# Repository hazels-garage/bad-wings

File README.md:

# Bad Wings

* [v2](/v2) - Current Hotness
* [v1](/v1) - The Original
* [slim](/slim) - ultrathin wireless
* [pocket](/pocket) - thumb keeb
* [pocket2](/pocket2) - better thumb keeb
* [go](/go) - wireless thumb keeb
* [bold](/bold) - Oops! All 1.25u!

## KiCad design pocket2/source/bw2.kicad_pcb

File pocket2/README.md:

# Bad Wings 2: Pocket 
"Pocket" "Sized" "Ergonomic" "Keyboard"

# Features
* 36 key, "mouse" switches.
* It's really small
* HAS DIODES!
* Fits in a wallet that's slightly larger than a normal wallet.
* Could be used as a keychain, I guess.
* [Open Source](source/)
## Cases
[Top](case/top.step)
[Bottom](case/bottom.step)

## Materials
* 1x Waveshare RP2040-Zero
* 36x "Kailh Mute Button 6x6x7.3 Silent Mouse Switch"
* 36x SOD-123 Diodes

## Build Guide
* Solder diodes
* Solder switches
* Solder RP2040-zero
* Flash [firmware](FIRMWARE.md)
* Done

### Warning
I slapped together this documentation so there is a good chance I've overlooked something.  Find me on Discord if you need help.

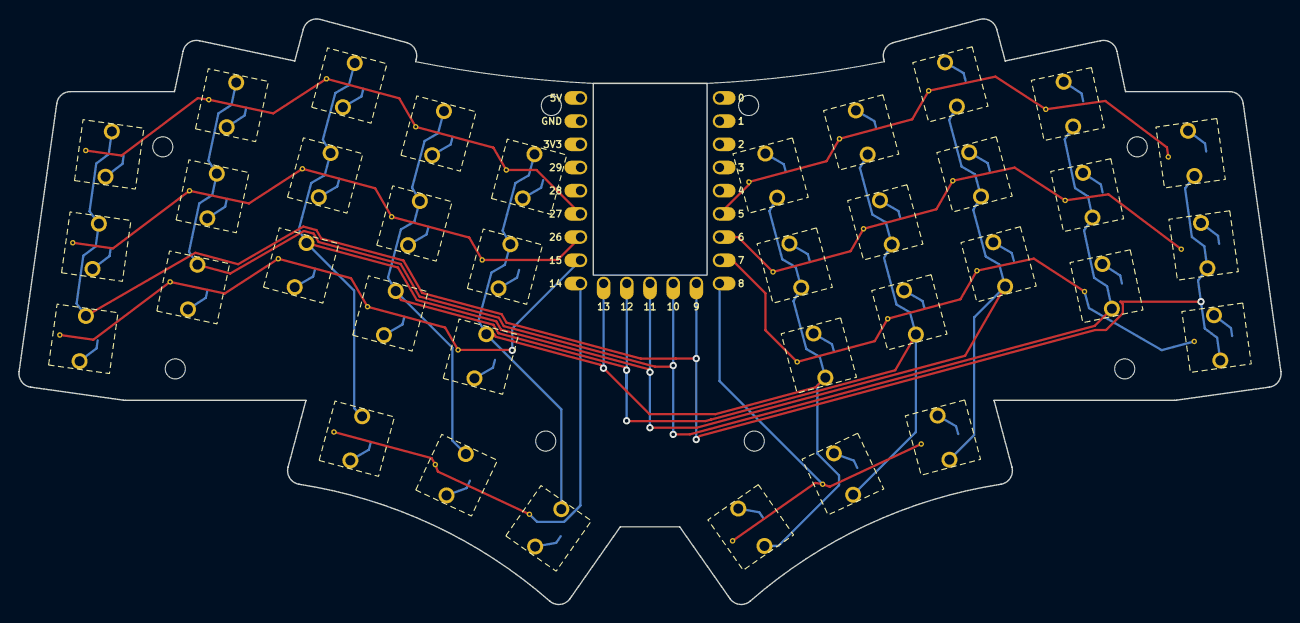
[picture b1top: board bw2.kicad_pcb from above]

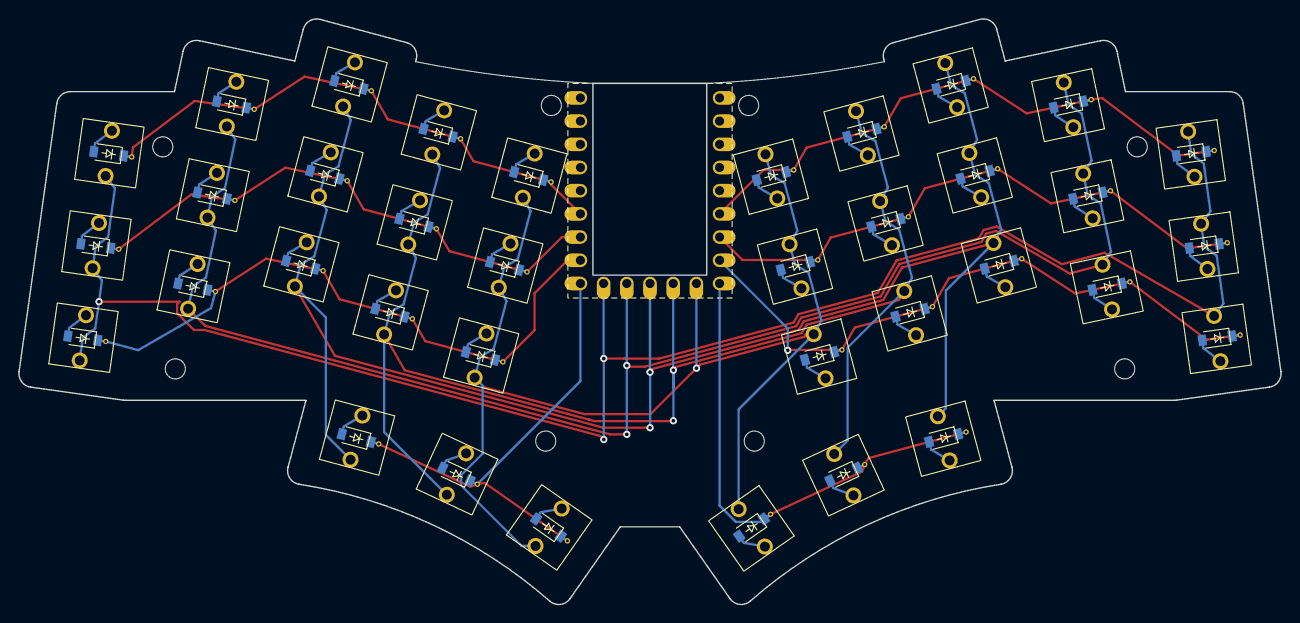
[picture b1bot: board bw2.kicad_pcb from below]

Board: 2 copper layers, 138.2 x 64.1 mm, 82 parts (44 on the bottom side), 49 nets.

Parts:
D1, D2, D3, D4, D5, D6, D7, D8, D9, D10, D11, D12, D13, D14, D15, D16, D17, D18, D19, D20, D21, D22, D23, D24, D25, D26, D27, D28, D29, D30, D31, D32, D33, D34, D35, D36: 1N4148W; D_SOD-123
H1, H2, H3, H4, H5, H6, H7, H8: MountingHole_2.2mm_M2
LOGO1: LOGO
SW1: [2,0]; Silent Square Micro Switch
SW2: [1,0]; Silent Square Micro Switch
SW3: [0,0]; Silent Square Micro Switch
SW4: [2,1]; Silent Square Micro Switch
SW5, SW8: [1,2]; Silent Square Micro Switch
SW6: [0,1]; Silent Square Micro Switch
SW7: [2,2]; Silent Square Micro Switch
SW9: [0,2]; Silent Square Micro Switch
SW10: [2,3]; Silent Square Micro Switch
SW11: [1,3]; Silent Square Micro Switch
SW12: [0,3]; Silent Square Micro Switch
SW13: [2,4]; Silent Square Micro Switch
SW14: [1,4]; Silent Square Micro Switch
SW15: [0,4]; Silent Square Micro Switch
SW16: [6,0]; Silent Square Micro Switch
SW17: [5,0]; Silent Square Micro Switch
SW18: [4,0]; Silent Square Micro Switch
SW19: [6,1]; Silent Square Micro Switch
SW20: [5,1]; Silent Square Micro Switch
SW21: [4,1]; Silent Square Micro Switch
SW22: [6,2]; Silent Square Micro Switch
SW23: [5,2]; Silent Square Micro Switch
SW24: [4,2]; Silent Square Micro Switch
SW25: [6,3]; Silent Square Micro Switch
SW26: [5,3]; Silent Square Micro Switch
SW27: [4,3]; Silent Square Micro Switch
SW28: [6,4]; Silent Square Micro Switch
SW29: [5,4]; Silent Square Micro Switch
SW30: [4,4]; Silent Square Micro Switch
SW31: [3,2]; Silent Square Micro Switch
SW32: [3,3]; Silent Square Micro Switch
SW33: [3,4]; Silent Square Micro Switch
SW34: [7,2]; Silent Square Micro Switch
SW35: [7,3]; Silent Square Micro Switch
SW36: [7,4]; Silent Square Micro Switch
U1: RP2040-Zero; rp2040-zero-facedown-swapped-5v-gnd

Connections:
COL0: SW1.2, SW2.2, SW3.2, SW16.2, SW17.2, SW18.2, U1.10 (GP9)
COL1: SW4.2, SW5.2, SW6.2, SW19.2, SW20.2, SW21.2, U1.11 (GP10)
COL2: SW7.2, SW8.2, SW9.2, SW22.2, SW23.2, SW24.2, SW31.2, SW34.2, U1.12 (GP11)
COL3: SW10.2, SW11.2, SW12.2, SW25.2, SW26.2, SW27.2, SW32.2, SW35.2, U1.13 (GP12)
COL4: SW13.2, SW14.2, SW15.2, SW28.2, SW29.2, SW30.2, SW33.2, SW36.2, U1.14 (GP13)
unnamed: D1.2 (A), SW1.1
unnamed: D2.2 (A), SW2.1
unnamed: D3.2 (A), SW3.1
unnamed: D4.2 (A), SW4.1
unnamed: D5.2 (A), SW5.1
unnamed: D6.2 (A), SW6.1
unnamed: D7.2 (A), SW7.1
unnamed: D8.2 (A), SW8.1
unnamed: D9.2 (A), SW9.1
unnamed: D10.2 (A), SW10.1
unnamed: D11.2 (A), SW11.1
unnamed: D12.2 (A), SW12.1
unnamed: D13.2 (A), SW13.1
unnamed: D14.2 (A), SW14.1
unnamed: D15.2 (A), SW15.1
unnamed: D16.2 (A), SW16.1
unnamed: D17.2 (A), SW17.1
unnamed: D18.2 (A), SW18.1
unnamed: D19.2 (A), SW19.1
unnamed: D20.2 (A), SW20.1
unnamed: D21.2 (A), SW21.1
unnamed: D22.2 (A), SW22.1
unnamed: D23.2 (A), SW23.1
unnamed: D24.2 (A), SW24.1
unnamed: D25.2 (A), SW25.1
unnamed: D26.2 (A), SW26.1
unnamed: D27.2 (A), SW27.1
unnamed: D28.2 (A), SW28.1
unnamed: D29.2 (A), SW29.1
unnamed: D30.2 (A), SW30.1
unnamed: D31.2 (A), SW31.1
unnamed: D32.2 (A), SW32.1
unnamed: D33.2 (A), SW33.1
unnamed: D34.2 (A), SW34.1
unnamed: D35.2 (A), SW35.1
unnamed: D36.2 (A), SW36.1
ROW0: D3.1 (K), D6.1 (K), D9.1 (K), D12.1 (K), D15.1 (K), U1.18 (GP27)
ROW1: D2.1 (K), D5.1 (K), D8.1 (K), D11.1 (K), D14.1 (K), U1.17 (GP26)
ROW2: D1.1 (K), D4.1 (K), D7.1 (K), D10.1 (K), D13.1 (K), U1.16 (GP15)
ROW3: D31.1 (K), D32.1 (K), D33.1 (K), U1.15 (GP14)
ROW4: D18.1 (K), D21.1 (K), D24.1 (K), D27.1 (K), D30.1 (K), U1.6 (GP5)
ROW5: D17.1 (K), D20.1 (K), D23.1 (K), D26.1 (K), D29.1 (K), U1.7 (GP6)
ROW6: D16.1 (K), D19.1 (K), D22.1 (K), D25.1 (K), D28.1 (K), U1.8 (GP7)
ROW7: D34.1 (K), D35.1 (K), D36.1 (K), U1.9 (GP8)

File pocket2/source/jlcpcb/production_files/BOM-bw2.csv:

Comment,Designator,Footprint,LCSC,Quantity
,H1,MountingHole_2.2mm_M2,,1
,H2,MountingHole_2.2mm_M2,,1
RP2040-Zero,U1,rp2040-zero-facedown-swapped-5v-gnd,,1
,H3,MountingHole_2.2mm_M2,,1
,H4,MountingHole_2.2mm_M2,,1
,H5,MountingHole_2.2mm_M2,,1
,H6,MountingHole_2.2mm_M2,,1
,H7,MountingHole_2.2mm_M2,,1
,H8,MountingHole_2.2mm_M2,,1
"[7,4]",SW36,Silent Square Micro Switch,,1
"[7,3]",SW35,Silent Square Micro Switch,,1
"[7,2]",SW34,Silent Square Micro Switch,,1
"[3,4]",SW33,Silent Square Micro Switch,,1
"[3,3]",SW32,Silent Square Micro Switch,,1
"[3,2]",SW31,Silent Square Micro Switch,,1
"[4,4]",SW30,Silent Square Micro Switch,,1
"[5,4]",SW29,Silent Square Micro Switch,,1
"[6,4]",SW28,Silent Square Micro Switch,,1
"[4,3]",SW27,Silent Square Micro Switch,,1
"[5,3]",SW26,Silent Square Micro Switch,,1
"[6,3]",SW25,Silent Square Micro Switch,,1
"[4,2]",SW24,Silent Square Micro Switch,,1
"[5,2]",SW23,Silent Square Micro Switch,,1
"[6,2]",SW22,Silent Square Micro Switch,,1
"[4,1]",SW21,Silent Square Micro Switch,,1
"[5,1]",SW20,Silent Square Micro Switch,,1
"[6,1]",SW19,Silent Square Micro Switch,,1
"[4,0]",SW18,Silent Square Micro Switch,,1
"[5,0]",SW17,Silent Square Micro Switch,,1
"[6,0]",SW16,Silent Square Micro Switch,,1
"[0,4]",SW15,Silent Square Micro Switch,,1
"[1,4]",SW14,Silent Square Micro Switch,,1
"[2,4]",SW13,Silent Square Micro Switch,,1
"[0,3]",SW12,Silent Square Micro Switch,,1
"[1,3]",SW11,Silent Square Micro Switch,,1
"[2,3]",SW10,Silent Square Micro Switch,,1
"[0,2]",SW9,Silent Square Micro Switch,,1
"[1,2]",SW8,Silent Square Micro Switch,,1
"[2,2]",SW7,Silent Square Micro Switch,,1
"[0,1]",SW6,Silent Square Micro Switch,,1
"[1,2]",SW5,Silent Square Micro Switch,,1
"[2,1]",SW4,Silent Square Micro Switch,,1
"[0,0]",SW3,Silent Square Micro Switch,,1
"[1,0]",SW2,Silent Square Micro Switch,,1
"[2,0]",SW1,Silent Square Micro Switch,,1
1N4148W,D36,D_SOD-123,,1
1N4148W,D35,D_SOD-123,,1
1N4148W,D34,D_SOD-123,,1
1N4148W,D33,D_SOD-123,,1
1N4148W,D32,D_SOD-123,,1
1N4148W,D31,D_SOD-123,,1
1N4148W,D30,D_SOD-123,,1
1N4148W,D29,D_SOD-123,,1
1N4148W,D28,D_SOD-123,,1
1N4148W,D27,D_SOD-123,,1
1N4148W,D26,D_SOD-123,,1
1N4148W,D25,D_SOD-123,,1
1N4148W,D24,D_SOD-123,,1
1N4148W,D23,D_SOD-123,,1
1N4148W,D22,D_SOD-123,,1
1N4148W,D21,D_SOD-123,,1
1N4148W,D20,D_SOD-123,,1
1N4148W,D19,D_SOD-123,,1
1N4148W,D18,D_SOD-123,,1
1N4148W,D17,D_SOD-123,,1
1N4148W,D16,D_SOD-123,,1
1N4148W,D15,D_SOD-123,,1
1N4148W,D14,D_SOD-123,,1
1N4148W,D13,D_SOD-123,,1
1N4148W,D12,D_SOD-123,,1
1N4148W,D11,D_SOD-123,,1
1N4148W,D10,D_SOD-123,,1
1N4148W,D9,D_SOD-123,,1
1N4148W,D8,D_SOD-123,,1
1N4148W,D7,D_SOD-123,,1
1N4148W,D6,D_SOD-123,,1
1N4148W,D5,D_SOD-123,,1
1N4148W,D4,D_SOD-123,,1
1N4148W,D3,D_SOD-123,,1
1N4148W,D2,D_SOD-123,,1
1N4148W,D1,D_SOD-123,,1
,LOGO1,LOGO,,1

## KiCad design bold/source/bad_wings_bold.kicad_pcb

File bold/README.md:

# Bad Wings: **Bold**
Oops! All 1.25u!

# Features
* 36key, "choc spaced", all 1.25u
* RP2040-Zero

# Materials
* 1x RP2040-zero
* 36x Choc v1 Switches
* 36x SOD-123 1N4148 Diodes
* 36x Hotswap Sockets (optional)

# Build Guide
* Install Diodes
* Install RP2040-zero (buttons facing up)
* Flash [Firmware](FIRMWARE.md)
* Test Matrix
  * use metal tweezers to short the connections for each switch on the PCB
* If matrix works, install switches
  * Hotswap Sockets optional
  * ALso mill-maxable
* Done

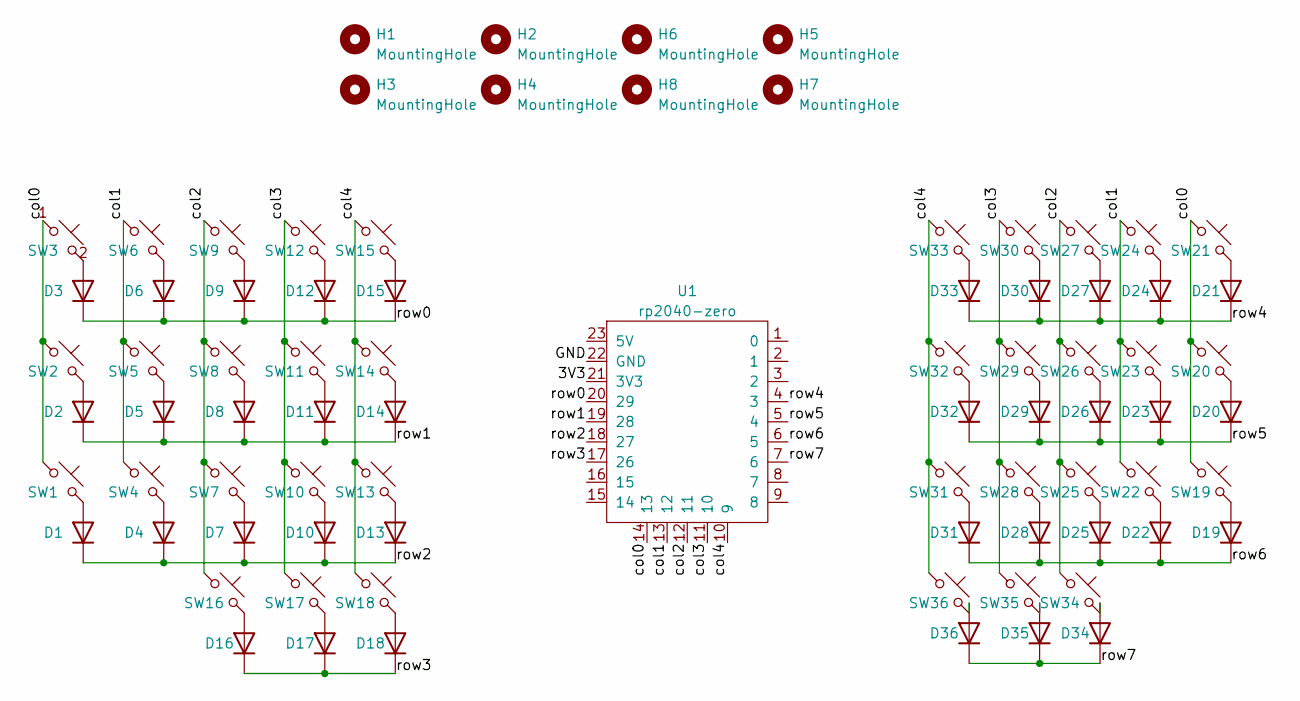
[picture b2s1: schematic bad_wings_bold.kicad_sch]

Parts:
D1, D2, D3, D4, D5, D6, D7, D8, D9, D10, D11, D12, D13, D14, D15, D16, D17, D18, D19, D20, D21, D22, D23, D24, D25, D26, D27, D28, D29, D30, D31, D32, D33, D34, D35, D36: 1N4148W; D_SOD-123
H1, H2, H3, H4, H5, H6, H7, H8: MountingHole; MountingHole_3.2mm_M3
SW1, SW2, SW3, SW4, SW5, SW6, SW7, SW8, SW9, SW10, SW11, SW12, SW13, SW14, SW15, SW16, SW17, SW18, SW19, SW20, SW21, SW22, SW23, SW24, SW25, SW26, SW27, SW28, SW29, SW30, SW31, SW32, SW33, SW34, SW35, SW36: SW_Push_45deg; Choc-1u-hotswap-solderable
U1: rp2040-zero; rp2040-zero-facedown

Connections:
/3V3: U1.21 (3V3)
/GND: U1.22 (GND)
/col0: SW1.1, SW2.1, SW3.1, SW19.1, SW20.1, SW21.1, U1.14 (13)
/col1: SW4.1, SW5.1, SW6.1, SW22.1, SW23.1, SW24.1, U1.13 (12)
/col2: SW7.1, SW8.1, SW9.1, SW16.1, SW25.1, SW26.1, SW27.1, SW34.1, U1.12 (11)
/col3: SW10.1, SW11.1, SW12.1, SW17.1, SW28.1, SW29.1, SW30.1, SW35.1, U1.11 (10)
/col4: SW13.1, SW14.1, SW15.1, SW18.1, SW31.1, SW32.1, SW33.1, SW36.1, U1.10 (9)
/row0: D3.1 (K), D6.1 (K), D9.1 (K), D12.1 (K), D15.1 (K), U1.20 (29)
/row1: D2.1 (K), D5.1 (K), D8.1 (K), D11.1 (K), D14.1 (K), U1.19 (28)
/row2: D1.1 (K), D4.1 (K), D7.1 (K), D10.1 (K), D13.1 (K), U1.18 (27)
/row3: D16.1 (K), D17.1 (K), D18.1 (K), U1.17 (26)
/row4: D21.1 (K), D24.1 (K), D27.1 (K), D30.1 (K), D33.1 (K), U1.4 (3)
/row5: D20.1 (K), D23.1 (K), D26.1 (K), D29.1 (K), D32.1 (K), U1.5 (4)
/row6: D19.1 (K), D22.1 (K), D25.1 (K), D28.1 (K), D31.1 (K), U1.6 (5)
/row7: D34.1 (K), D35.1 (K), D36.1 (K), U1.7 (6)
unnamed: D1.2 (A), SW1.2
unnamed: D2.2 (A), SW2.2
unnamed: D3.2 (A), SW3.2
unnamed: D4.2 (A), SW4.2
unnamed: D5.2 (A), SW5.2
unnamed: D6.2 (A), SW6.2
unnamed: D7.2 (A), SW7.2
unnamed: D8.2 (A), SW8.2
unnamed: D9.2 (A), SW9.2
unnamed: D10.2 (A), SW10.2
unnamed: D11.2 (A), SW11.2
unnamed: D12.2 (A), SW12.2
unnamed: D13.2 (A), SW13.2
unnamed: D14.2 (A), SW14.2
unnamed: D15.2 (A), SW15.2
unnamed: D16.2 (A), SW16.2
unnamed: D17.2 (A), SW17.2
unnamed: D18.2 (A), SW18.2
unnamed: D19.2 (A), SW19.2
unnamed: D20.2 (A), SW20.2
unnamed: D21.2 (A), SW21.2
unnamed: D22.2 (A), SW22.2
unnamed: D23.2 (A), SW23.2
unnamed: D24.2 (A), SW24.2
unnamed: D25.2 (A), SW25.2
unnamed: D26.2 (A), SW26.2
unnamed: D27.2 (A), SW27.2
unnamed: D28.2 (A), SW28.2
unnamed: D29.2 (A), SW29.2
unnamed: D30.2 (A), SW30.2
unnamed: D31.2 (A), SW31.2
unnamed: D32.2 (A), SW32.2
unnamed: D33.2 (A), SW33.2
unnamed: D34.2 (A), SW34.2
unnamed: D35.2 (A), SW35.2
unnamed: D36.2 (A), SW36.2

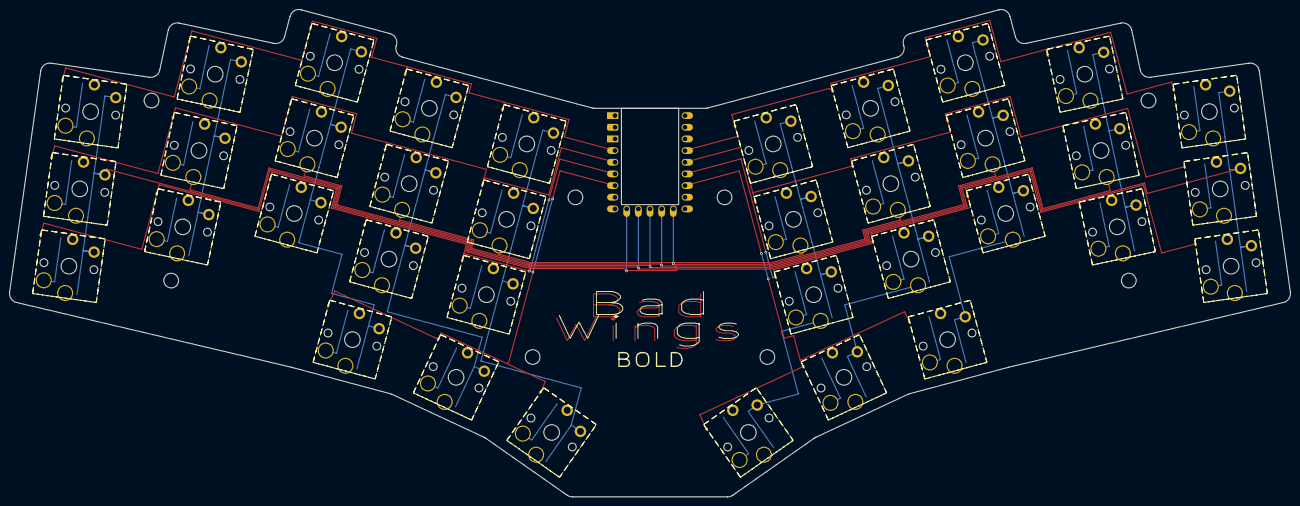
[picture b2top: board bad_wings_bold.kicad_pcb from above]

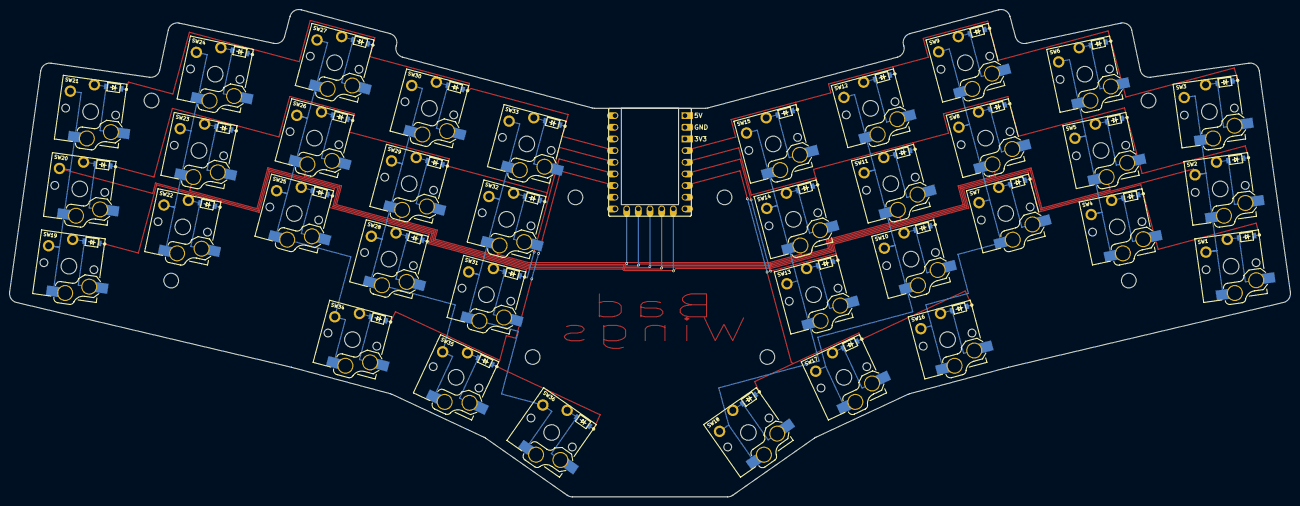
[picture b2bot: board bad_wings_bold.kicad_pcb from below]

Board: 2 copper layers, 279.0 x 106.2 mm, 81 parts (36 on the bottom side), 49 nets.

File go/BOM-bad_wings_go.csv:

Comment,Designator,Footprint,LCSC
SW_Push_45deg,"SW1,SW10,SW11,SW12,SW13,SW14,SW15,SW16,SW17,SW18,SW19,SW2,SW20,SW21,SW22,SW23,SW24,SW25,SW26,SW27,SW28,SW29,SW3,SW30,SW31,SW32,SW33,SW34,SW35,SW36,SW4,SW5,SW6,SW7,SW8,SW9",SW_SPST_TL3342,C115351
SW_SPDT,PWR1,SPDT_C128955,C128955
1N4148W,BD1,D_SOD-123,C81598
xiao-ble,U1,xiao-ble-smd-cutout,

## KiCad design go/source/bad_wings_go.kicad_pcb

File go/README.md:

# Bad Wings: Go
Wireless "Pocket" "Sized" "Ergonomic" "Keyboard"

# Features
* 36 key, 4x4mm switches.
* It's really small
* No diodes, so don't try to type fast
* Fits in a wallet that's slightly larger than a normal wallet.
* Could be used as a keychain, I guess.
* [Open Source](source/)

## Materials
* 1x XIAO BLE
* 1x SOD-123 1N4148 Diode
* 36x SKQGAFE010 TACT Switch
* 1x MSK-12C02 Power Switch
* 1x [CR2032 Battery Holder](https://www.aliexpress.us/item/2251832843180857.html)
## Build Guide
* Solder switches
* Solder XIAO
  * Surface mounted on top of PCB
  * Solder BAT and NFC pads from back of PCB
* Flash [firmware](FIRMWARE.md)
* Solder CR2032 holder
* Solder battery diode
* Solder Power Switch
* Insert Battery
* Done

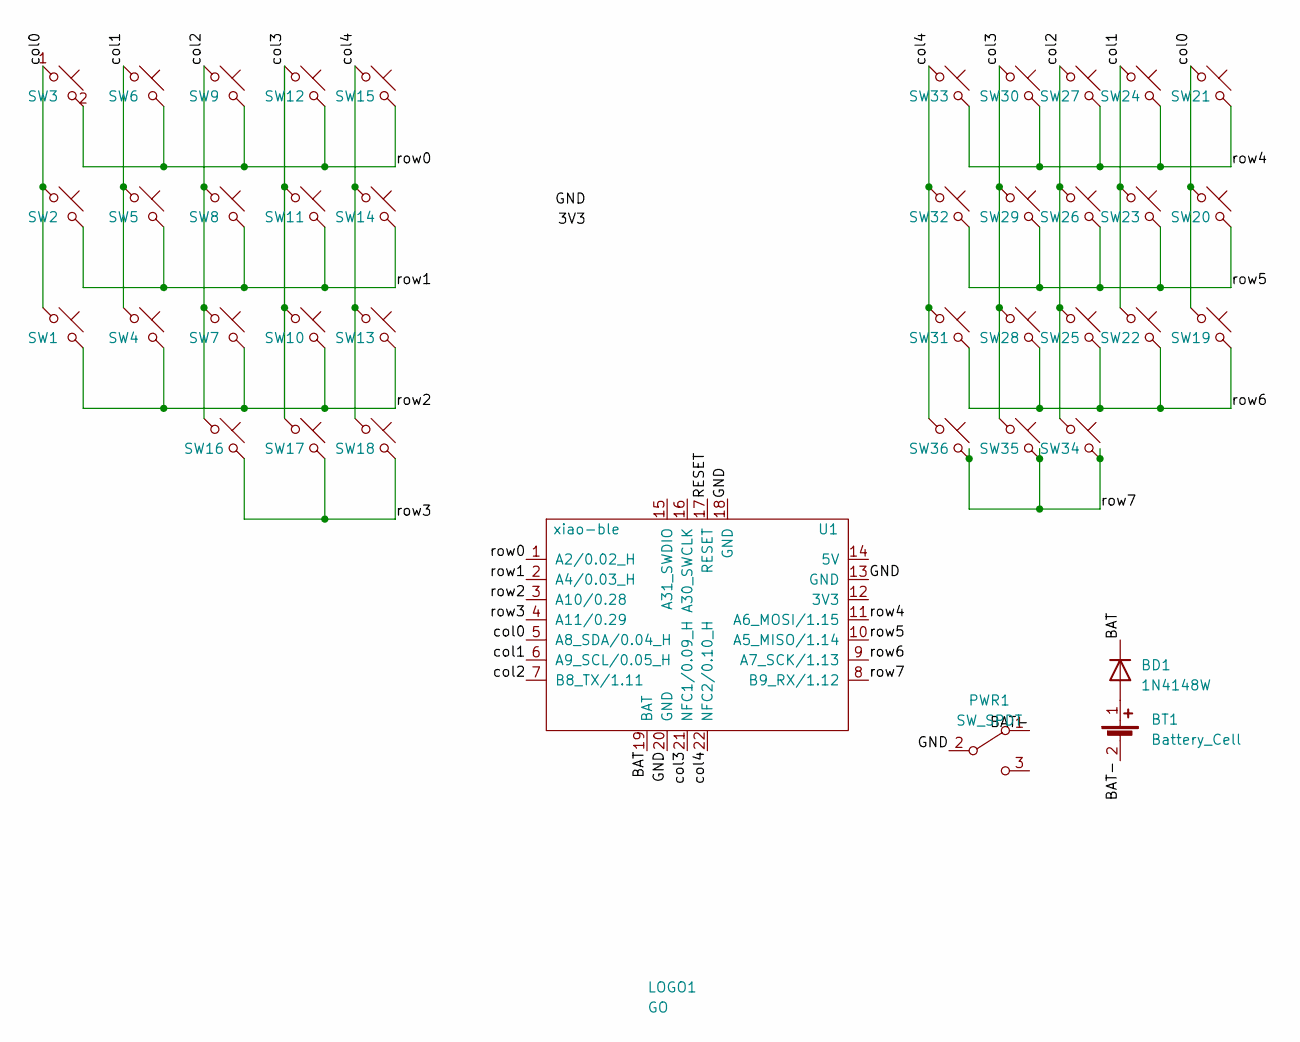
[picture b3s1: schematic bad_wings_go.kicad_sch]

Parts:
BD1: 1N4148W; D_SOD-123
BT1: Battery_Cell; BatteryHolder_Keystone_3002_1x2032
LOGO1: GO; logo
PWR1: SW_SPDT; SPDT_C128955
SW1, SW2, SW3, SW4, SW5, SW6, SW7, SW8, SW9, SW10, SW11, SW12, SW13, SW14, SW15, SW16, SW17, SW18, SW19, SW20, SW21, SW22, SW23, SW24, SW25, SW26, SW27, SW28, SW29, SW30, SW31, SW32, SW33, SW34, SW35, SW36: SW_Push_45deg; SW_SPST_TL3342
U1: xiao-ble; xiao-ble-smd-cutout

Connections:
/BAT: BD1.1 (K), U1.19 (BAT)
/BAT-: BT1.2 (-), PWR1.1 (A)
/GND: PWR1.2 (B), U1.13 (GND), U1.18 (GND), U1.20 (GND)
/RESET: U1.17 (RESET)
/col0: SW1.1, SW2.1, SW3.1, SW19.1, SW20.1, SW21.1, U1.5 (A8_SDA/0.04_H)
/col1: SW4.1, SW5.1, SW6.1, SW22.1, SW23.1, SW24.1, U1.6 (A9_SCL/0.05_H)
/col2: SW7.1, SW8.1, SW9.1, SW16.1, SW25.1, SW26.1, SW27.1, SW34.1, U1.7 (B8_TX/1.11)
/col3: SW10.1, SW11.1, SW12.1, SW17.1, SW28.1, SW29.1, SW30.1, SW35.1, U1.21 (NFC1/0.09_H)
/col4: SW13.1, SW14.1, SW15.1, SW18.1, SW31.1, SW32.1, SW33.1, SW36.1, U1.22 (NFC2/0.10_H)
/row0: SW3.2, SW6.2, SW9.2, SW12.2, SW15.2, U1.1 (A2/0.02_H)
/row1: SW2.2, SW5.2, SW8.2, SW11.2, SW14.2, U1.2 (A4/0.03_H)
/row2: SW1.2, SW4.2, SW7.2, SW10.2, SW13.2, U1.3 (A10/0.28)
/row3: SW16.2, SW17.2, SW18.2, U1.4 (A11/0.29)
/row4: SW21.2, SW24.2, SW27.2, SW30.2, SW33.2, U1.11 (A6_MOSI/1.15)
/row5: SW20.2, SW23.2, SW26.2, SW29.2, SW32.2, U1.10 (A5_MISO/1.14)
/row6: SW19.2, SW22.2, SW25.2, SW28.2, SW31.2, U1.9 (A7_SCK/1.13)
/row7: SW34.2, SW35.2, SW36.2, U1.8 (B9_RX/1.12)
unnamed: BD1.2 (A), BT1.1 (+)

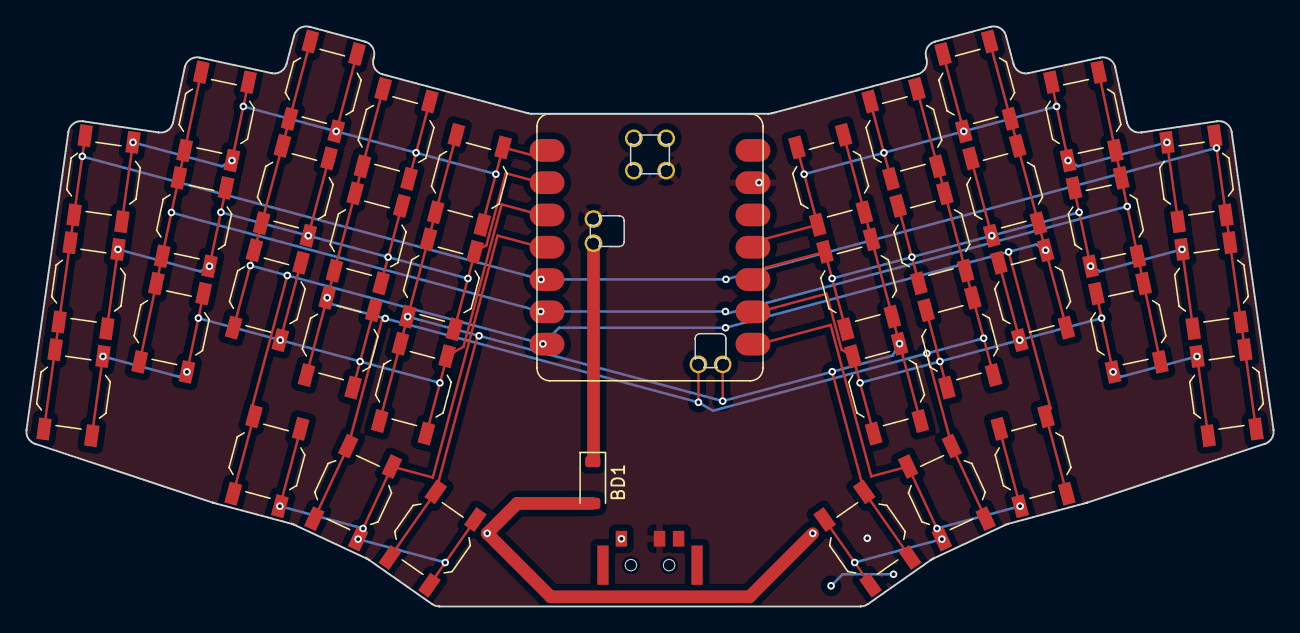
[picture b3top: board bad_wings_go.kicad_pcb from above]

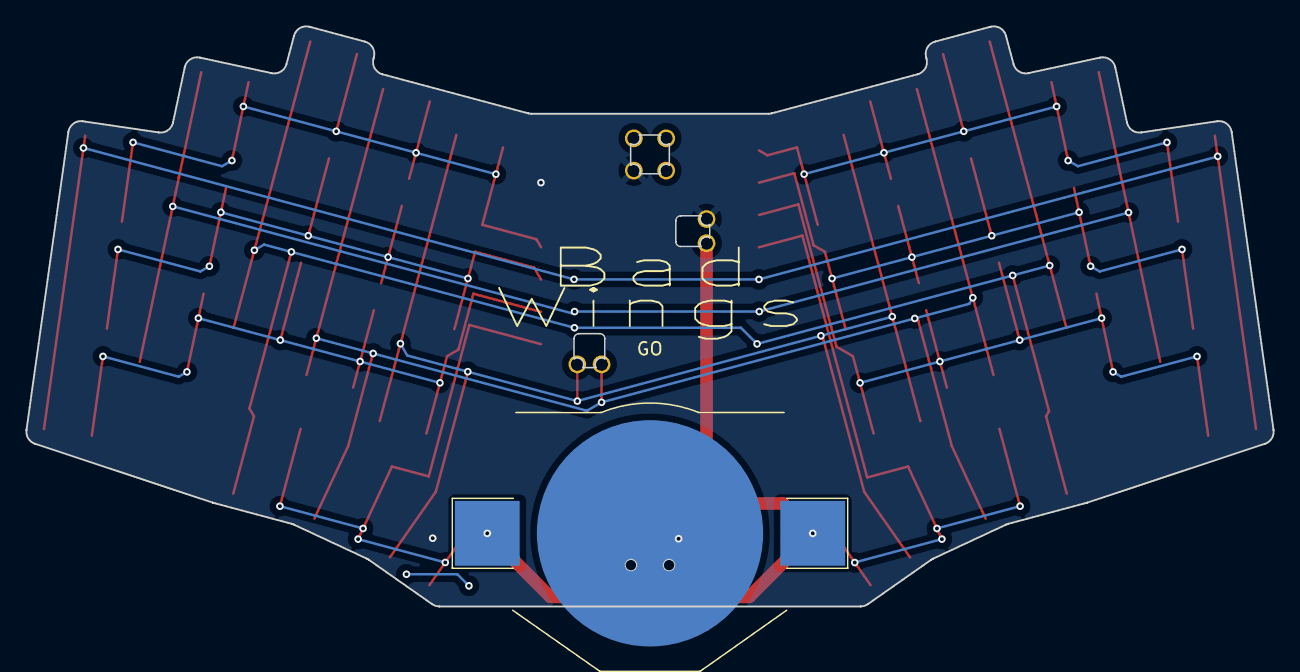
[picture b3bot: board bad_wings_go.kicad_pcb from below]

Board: 2 copper layers, 98.1 x 45.6 mm, 41 parts (2 on the bottom side), 17 nets.

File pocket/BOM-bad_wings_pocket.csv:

Comment,Designator,Footprint,LCSC
SW_Push_45deg,"SW1,SW10,SW11,SW12,SW13,SW14,SW15,SW16,SW17,SW18,SW19,SW2,SW20,SW21,SW22,SW23,SW24,SW25,SW26,SW27,SW28,SW29,SW3,SW30,SW31,SW32,SW33,SW34,SW35,SW36,SW4,SW5,SW6,SW7,SW8,SW9",POCKET-SWITCH,C202424

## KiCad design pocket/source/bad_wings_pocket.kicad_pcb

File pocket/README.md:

# Bad Wings: Pocket
"Pocket" "Sized" "Ergonomic" "Keyboard"

# Features
* 36 key, 4x4mm switches.
* It's really small
* No diodes, so don't try to type fast
* Fits in a wallet that's slightly larger than a normal wallet.
* Could be used as a keychain, I guess.
* [Open Source](source/)
## Cases
[Pressfit](cases/pressfit.stl)

## Materials
* 1x Waveshare RP2040-Zero
* 36x SKQGAFE010 TACT Switch

## Build Guide
* Solder switches
* Solder RP2040-zero
* Flash [firmware](FIRMWARE.md)
* Done

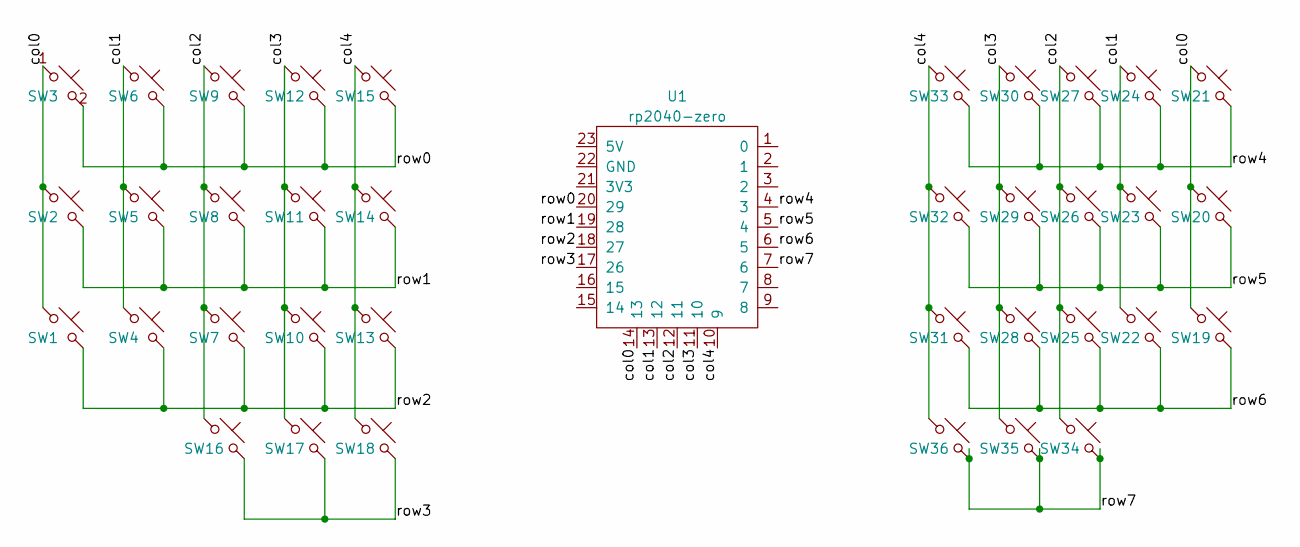
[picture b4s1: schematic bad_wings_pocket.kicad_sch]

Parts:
SW1, SW2, SW3, SW4, SW5, SW6, SW7, SW8, SW9, SW10, SW11, SW12, SW13, SW14, SW15, SW16, SW17, SW18, SW19, SW20, SW21, SW22, SW23, SW24, SW25, SW26, SW27, SW28, SW29, SW30, SW31, SW32, SW33, SW34, SW35, SW36: SW_Push_45deg; SW_SPST_TL3342
U1: rp2040-zero; rp2040-zero-facedown

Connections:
/col0: SW1.1, SW2.1, SW3.1, SW19.1, SW20.1, SW21.1, U1.14 (13)
/col1: SW4.1, SW5.1, SW6.1, SW22.1, SW23.1, SW24.1, U1.13 (12)
/col2: SW7.1, SW8.1, SW9.1, SW16.1, SW25.1, SW26.1, SW27.1, SW34.1, U1.12 (11)
/col3: SW10.1, SW11.1, SW12.1, SW17.1, SW28.1, SW29.1, SW30.1, SW35.1, U1.11 (10)
/col4: SW13.1, SW14.1, SW15.1, SW18.1, SW31.1, SW32.1, SW33.1, SW36.1, U1.10 (9)
/row0: SW3.2, SW6.2, SW9.2, SW12.2, SW15.2, U1.20 (29)
/row1: SW2.2, SW5.2, SW8.2, SW11.2, SW14.2, U1.19 (28)
/row2: SW1.2, SW4.2, SW7.2, SW10.2, SW13.2, U1.18 (27)
/row3: SW16.2, SW17.2, SW18.2, U1.17 (26)
/row4: SW21.2, SW24.2, SW27.2, SW30.2, SW33.2, U1.4 (3)
/row5: SW20.2, SW23.2, SW26.2, SW29.2, SW32.2, U1.5 (4)
/row6: SW19.2, SW22.2, SW25.2, SW28.2, SW31.2, U1.6 (5)
/row7: SW34.2, SW35.2, SW36.2, U1.7 (6)

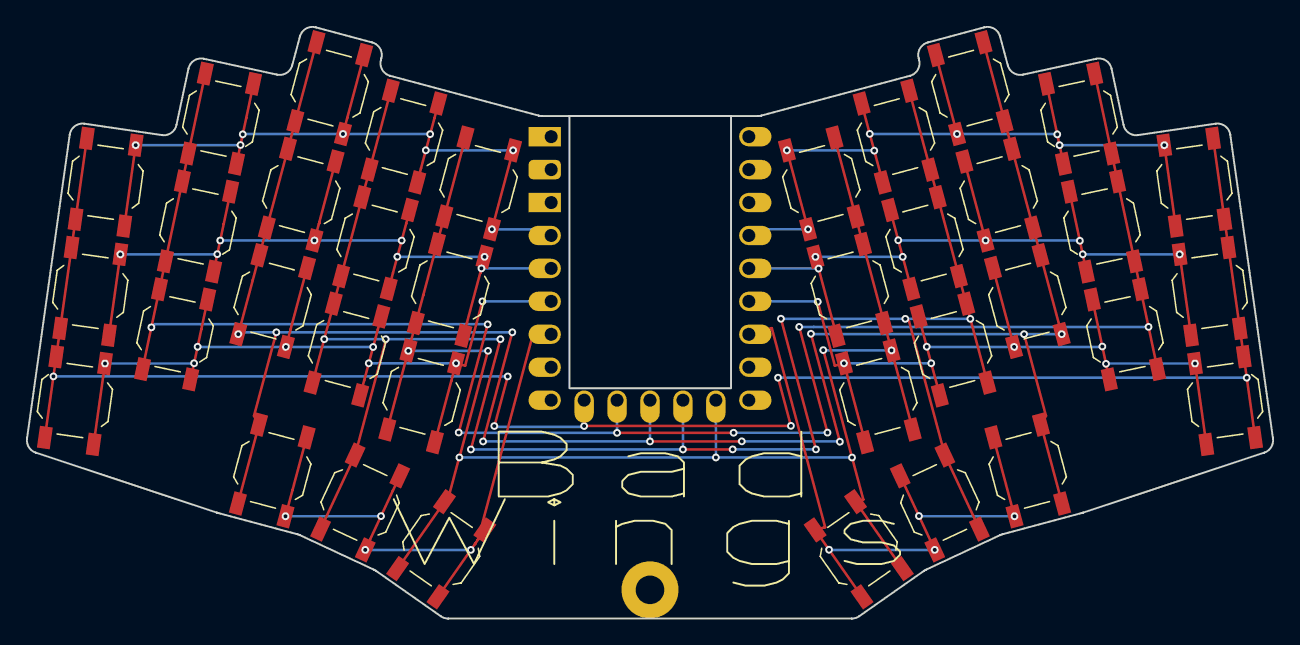
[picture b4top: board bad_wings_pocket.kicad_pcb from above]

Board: 2 copper layers, 96.1 x 45.6 mm, 38 parts (0 on the bottom side), 13 nets.

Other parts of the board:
H2: MountingHole; MountingHole_2.2mm_M2_Pad

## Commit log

2023-05-05 init
2023-05-18 more OG documentation, adding slim docs
2023-05-18 add materials
2023-05-18 add zmk config link
2023-05-18 rearrange gerber location
2023-05-18 rearrange images
2023-05-18 move link
2023-05-18 adding pocket
2023-05-18 update top readme
2023-05-23 adding go docs
2023-05-23 fix readme
2023-05-25 add bold
2023-05-25 update main readme
2023-05-25 typo and formatting fix
2023-07-23 up vial layers to 6
2023-08-13 add v1 case step files
2023-08-15 add pcb step to cases dir
2024-04-20 first pass at v2 stuff
2024-05-24 notes on cirque installation
2024-06-26 add v1 ble case top
2024-06-27 typofix
2024-08-03 case step files added
2024-09-04 adding miryoku
2024-09-13 adding v1 production files
2024-09-13 CC-BY-NC-SA
2024-09-13 updating readmes
2024-11-04 adding v2 source
2025-04-21 changing image
2025-06-26 Update README.md
    remove store link
2025-06-26 Update LICENSE.txt
    CC-BY-SA
2025-09-06 adding bw2 pocket
2025-09-06 readme
2025-09-06 update case links
2025-09-09 Update README.md
    remove NC from license on pocket2

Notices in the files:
README.md:
https://img.shields.io/badge/CC--BY--SA-test?style=flat-square&logo=creativecommons&logoColor=ffffff&label=%20&labelColor=8CBA04&color=8CBA04
